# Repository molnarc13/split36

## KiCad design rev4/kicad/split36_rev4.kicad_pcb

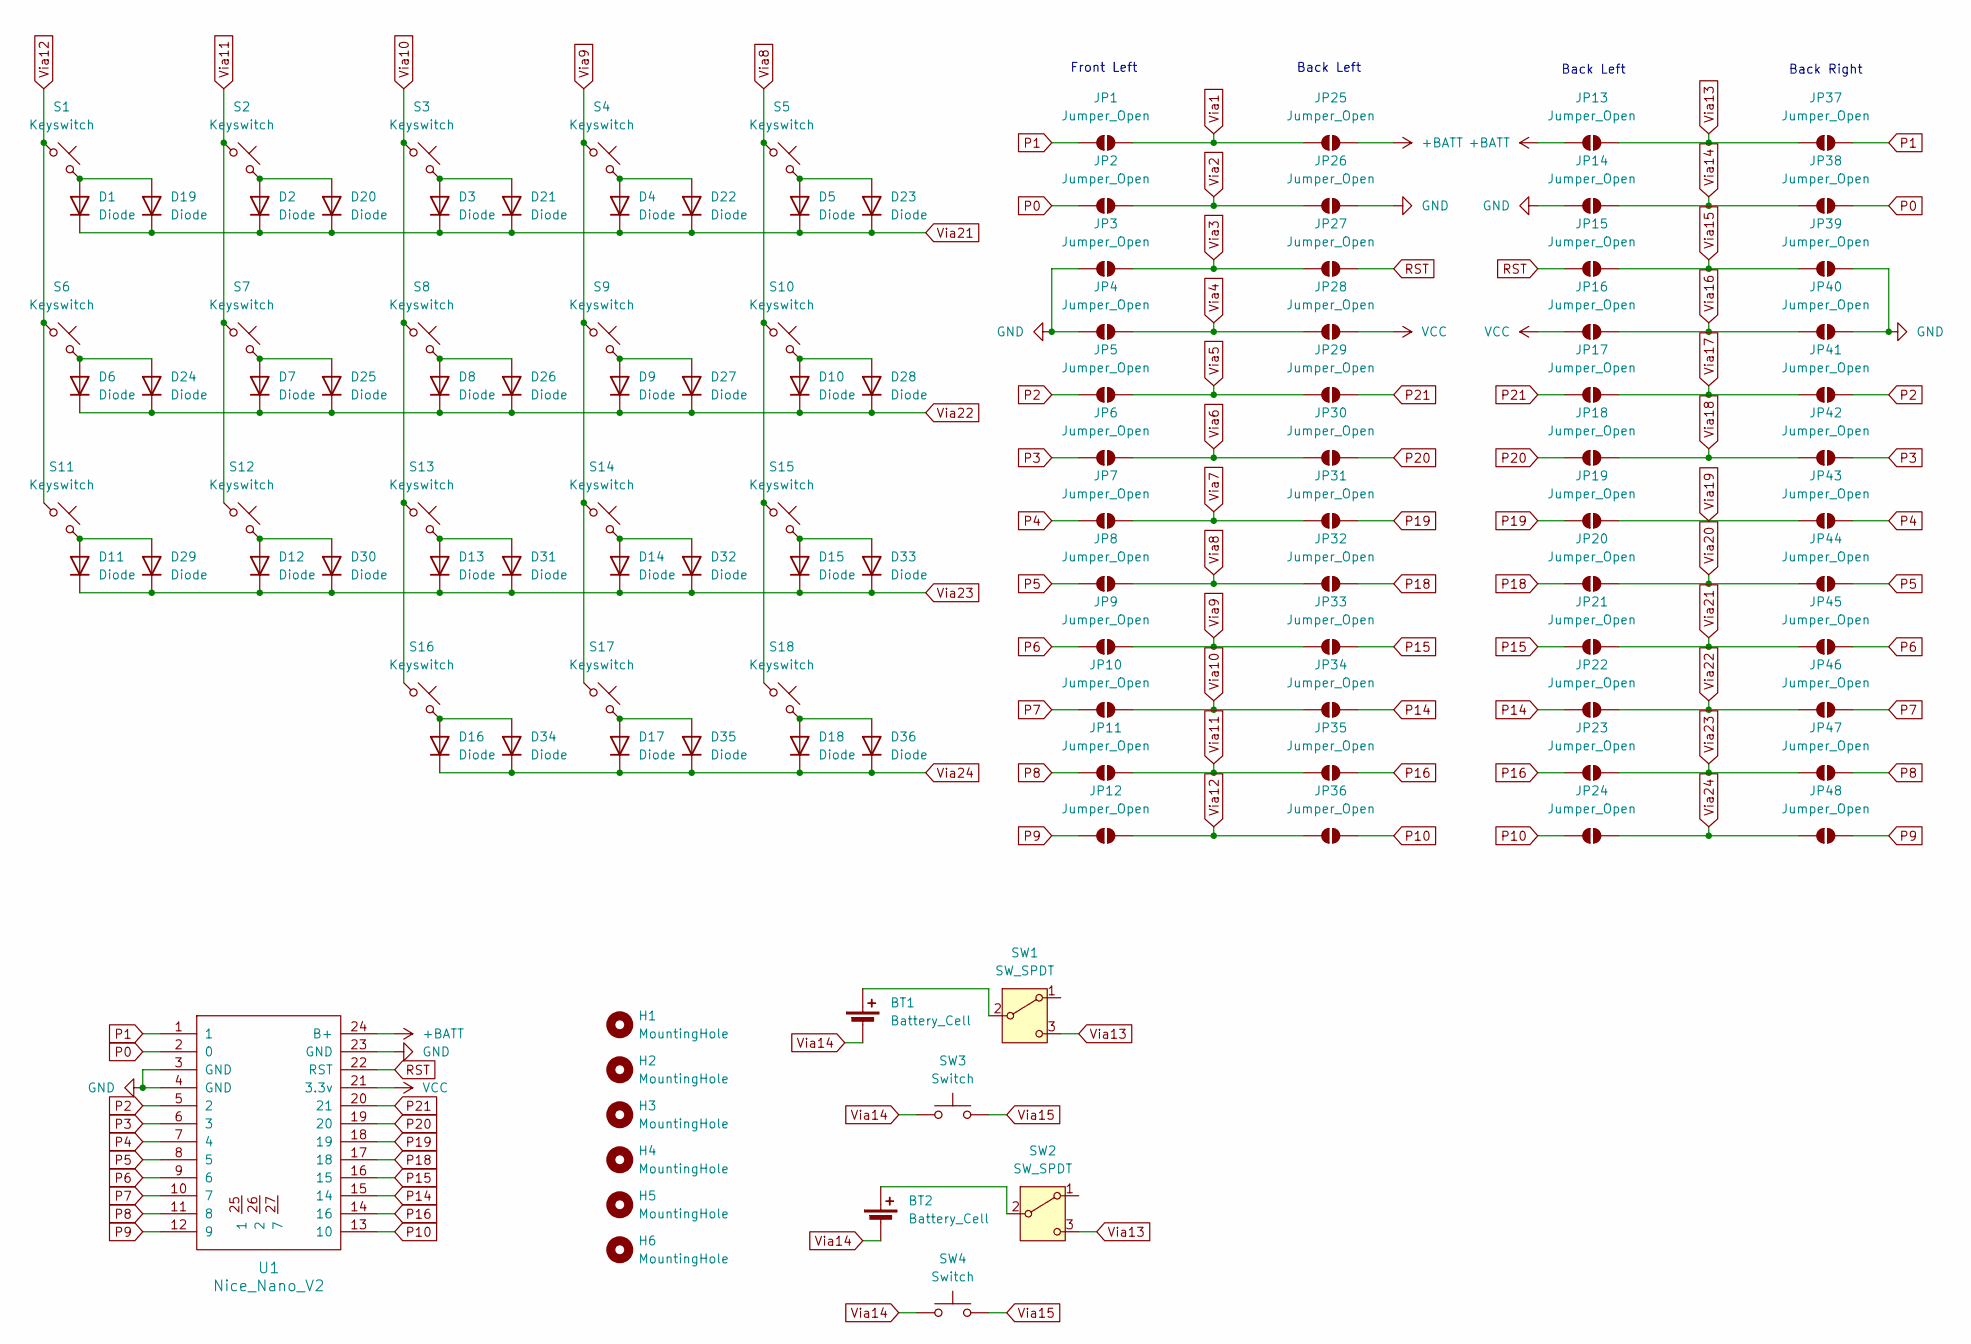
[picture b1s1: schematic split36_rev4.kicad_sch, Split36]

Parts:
BT1, BT2: Battery_Cell; JST_PH_S2B-PH-K_1x02_P2.00mm_Horizontal
D1, D2, D3, D4, D5, D6, D7, D8, D9, D10, D11, D12, D13, D14, D15, D16, D17, D18, D19, D20, D21, D22, D23, D24, D25, D26, D27, D28, D29, D30, D31, D32, D33, D34, D35, D36: Diode; Diode_SOD-123
H1, H2, H3, H4, H5, H6: MountingHole; Standoff_M2x6mm
JP1, JP2, JP3, JP4, JP5, JP6, JP7, JP8, JP9, JP10, JP11, JP12, JP13, JP14, JP15, JP16, JP17, JP18, JP19, JP20, JP21, JP22, JP23, JP24, JP25, JP26, JP27, JP28, JP29, JP30, JP31, JP32, JP33, JP34, JP35, JP36, JP37, JP38, JP39, JP40, JP41, JP42, JP43, JP44, JP45, JP46, JP47, JP48: Jumper_Open; SolderJumper-2_P1.3mm_Open_TrianglePad1.0x1.5mm
S1, S2, S3, S4, S5, S6, S7, S8, S9, S10, S11, S12, S13, S14, S15, S16, S17, S18: Keyswitch; Kailh_socket_PG1350_reversible
SW1, SW2: SW_SPDT; Switch_MSK12C02
SW3, SW4: Switch; SW_SPST_TL3342
U1: Nice_Nano_V2

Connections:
+BATT: JP13.1 (A), JP25.1 (A), U1.24 (B+)
GND: JP3.1 (A), JP4.1 (A), JP14.1 (A), JP26.1 (A), JP39.1 (A), JP40.1 (A), U1.3 (GND), U1.4 (GND), U1.23 (GND)
unnamed: BT1.1 (+), SW1.2 (B)
unnamed: BT2.1 (+), SW2.2 (B)
unnamed: D1.2 (A), D19.2 (A), S1.2
unnamed: D2.2 (A), D20.2 (A), S2.2
unnamed: D10.2 (A), D28.2 (A), S10.2
unnamed: D11.2 (A), D29.2 (A), S11.2
unnamed: D12.2 (A), D30.2 (A), S12.2
unnamed: D13.2 (A), D31.2 (A), S13.2
unnamed: D14.2 (A), D32.2 (A), S14.2
unnamed: D15.2 (A), D33.2 (A), S15.2
unnamed: D16.2 (A), D34.2 (A), S16.2
unnamed: D17.2 (A), D35.2 (A), S17.2
unnamed: D18.2 (A), D36.2 (A), S18.2
unnamed: D3.2 (A), D21.2 (A), S3.2
unnamed: D4.2 (A), D22.2 (A), S4.2
unnamed: D5.2 (A), D23.2 (A), S5.2
unnamed: D6.2 (A), D24.2 (A), S6.2
unnamed: D7.2 (A), D25.2 (A), S7.2
unnamed: D8.2 (A), D26.2 (A), S8.2
unnamed: D9.2 (A), D27.2 (A), S9.2
P0: JP2.1 (A), JP38.1 (A), U1.2 (0)
P1: JP1.1 (A), JP37.1 (A), U1.1
P2: JP5.1 (A), JP41.1 (A), U1.5 (2)
P3: JP6.1 (A), JP42.1 (A), U1.6 (3)
P4: JP7.1 (A), JP43.1 (A), U1.7 (4)
P5: JP8.1 (A), JP44.1 (A), U1.8 (5)
P6: JP9.1 (A), JP45.1 (A), U1.9 (6)
P7: JP10.1 (A), JP46.1 (A), U1.10 (7)
P8: JP11.1 (A), JP47.1 (A), U1.11 (8)
P9: JP12.1 (A), JP48.1 (A), U1.12 (9)
P10: JP24.1 (A), JP36.1 (A), U1.13 (10)
P14: JP22.1 (A), JP34.1 (A), U1.15 (14)
P15: JP21.1 (A), JP33.1 (A), U1.16 (15)
P16: JP23.1 (A), JP35.1 (A), U1.14 (16)
P18: JP20.1 (A), JP32.1 (A), U1.17 (18)
P19: JP19.1 (A), JP31.1 (A), U1.18 (19)
P20: JP18.1 (A), JP30.1 (A), U1.19 (20)
P21: JP17.1 (A), JP29.1 (A), U1.20 (21)
RST: JP15.1 (A), JP27.1 (A), U1.22 (RST)
VCC: JP16.1 (A), JP28.1 (A), U1.21 (3.3v)
Via1: JP1.2 (B), JP25.2 (B)
Via2: JP2.2 (B), JP26.2 (B)
Via3: JP3.2 (B), JP27.2 (B)
Via4: JP4.2 (B), JP28.2 (B)
Via5: JP5.2 (B), JP29.2 (B)
Via6: JP6.2 (B), JP30.2 (B)
Via7: JP7.2 (B), JP31.2 (B)
Via8: JP8.2 (B), JP32.2 (B), S5.1, S10.1, S15.1, S18.1
Via9: JP9.2 (B), JP33.2 (B), S4.1, S9.1, S14.1, S17.1
Via10: JP10.2 (B), JP34.2 (B), S3.1, S8.1, S13.1, S16.1
Via11: JP11.2 (B), JP35.2 (B), S2.1, S7.1, S12.1
Via12: JP12.2 (B), JP36.2 (B), S1.1, S6.1, S11.1
Via13: JP13.2 (B), JP37.2 (B), SW1.3 (C), SW2.3 (C)
Via14: BT1.2 (-), BT2.2 (-), JP14.2 (B), JP38.2 (B), SW3.1, SW4.1
Via15: JP15.2 (B), JP39.2 (B), SW3.2, SW4.2
Via16: JP16.2 (B), JP40.2 (B)
Via17: JP17.2 (B), JP41.2 (B)
Via18: JP18.2 (B), JP42.2 (B)
Via19: JP19.2 (B), JP43.2 (B)
Via20: JP20.2 (B), JP44.2 (B)
Via21: D1.1 (K), D2.1 (K), D3.1 (K), D4.1 (K), D5.1 (K), D19.1 (K), D20.1 (K), D21.1 (K), D22.1 (K), D23.1 (K), JP21.2 (B), JP45.2 (B)
Via22: D6.1 (K), D7.1 (K), D8.1 (K), D9.1 (K), D10.1 (K), D24.1 (K), D25.1 (K), D26.1 (K), D27.1 (K), D28.1 (K), JP22.2 (B), JP46.2 (B)
Via23: D11.1 (K), D12.1 (K), D13.1 (K), D14.1 (K), D15.1 (K), D29.1 (K), D30.1 (K), D31.1 (K), D32.1 (K), D33.1 (K), JP23.2 (B), JP47.2 (B)
Via24: D16.1 (K), D17.1 (K), D18.1 (K), D34.1 (K), D35.1 (K), D36.1 (K), JP24.2 (B), JP48.2 (B)

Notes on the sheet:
Back Left
Back Right
Front Left

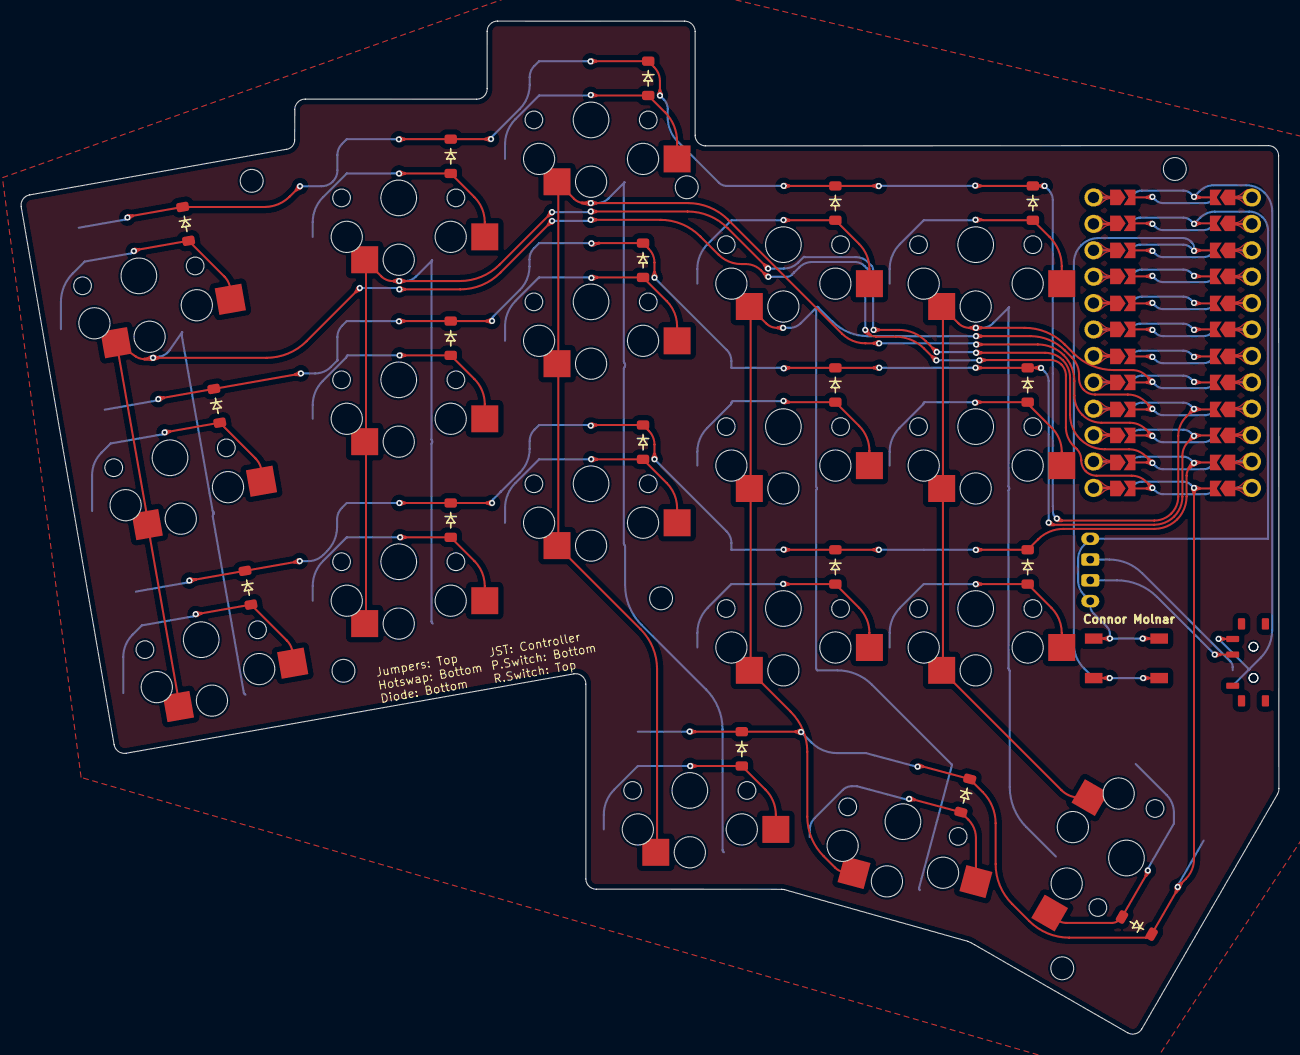
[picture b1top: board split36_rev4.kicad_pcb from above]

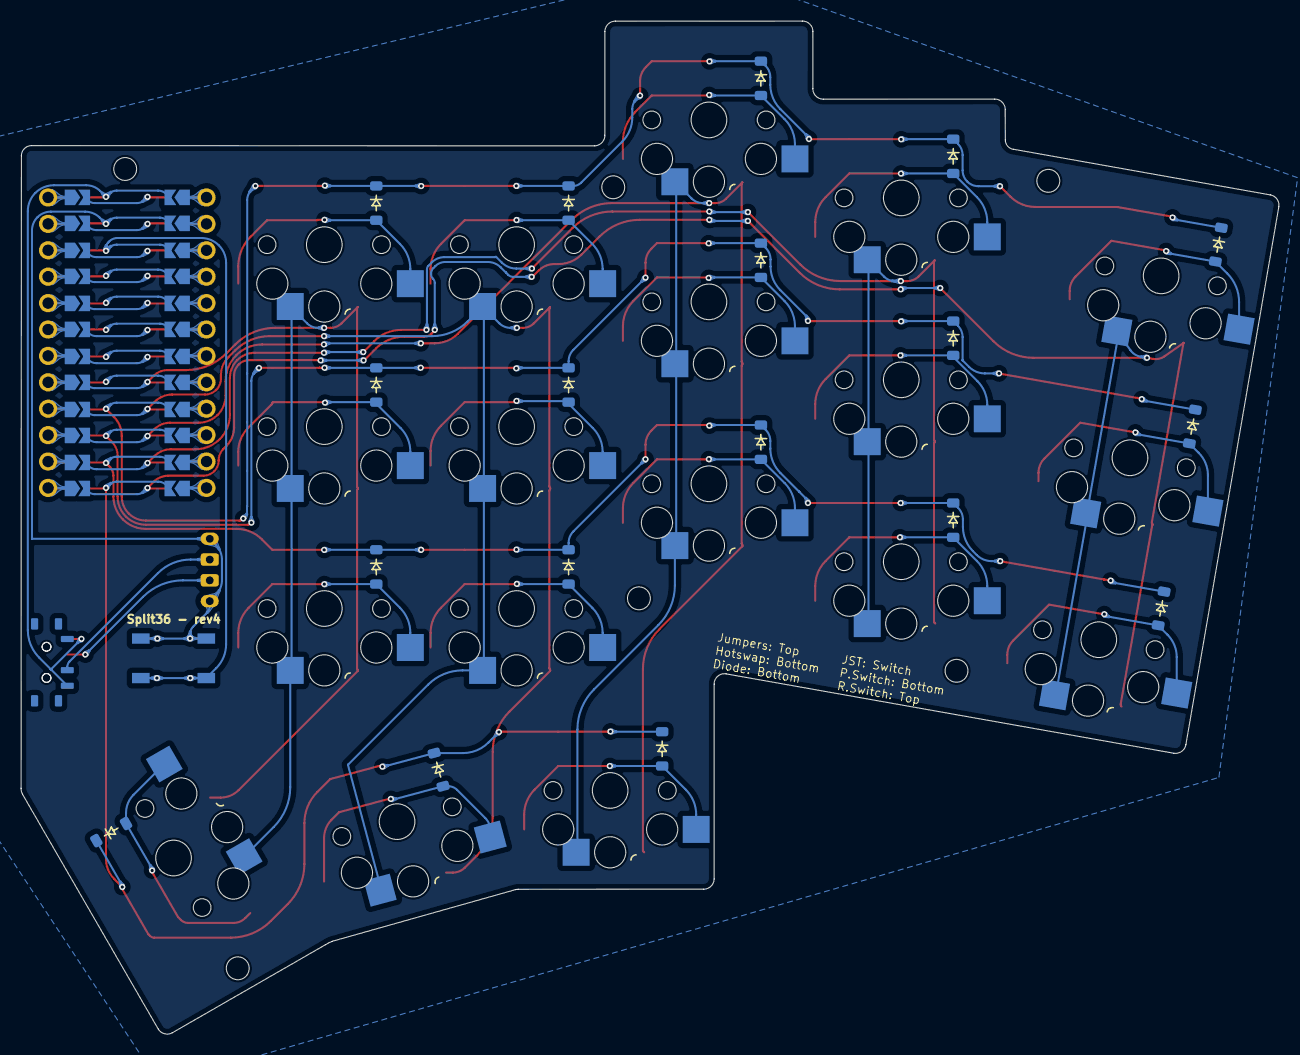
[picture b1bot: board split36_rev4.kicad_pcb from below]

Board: 2 copper layers, 121.0 x 97.4 mm, 115 parts (45 on the bottom side), 66 nets.

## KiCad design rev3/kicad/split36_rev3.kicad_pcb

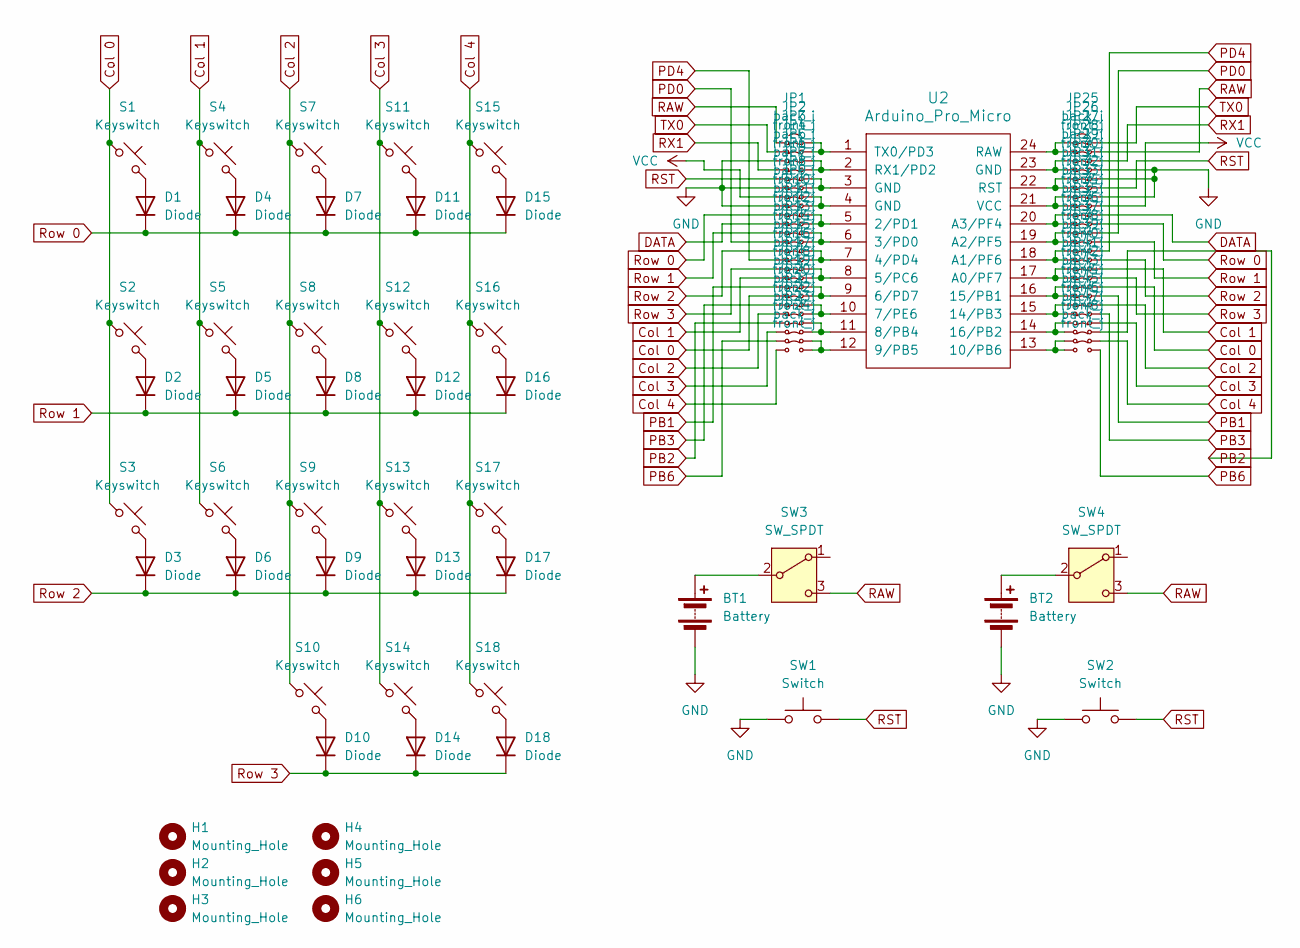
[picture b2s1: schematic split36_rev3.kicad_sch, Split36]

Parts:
BT1, BT2: Battery; JST_PH_S2B-PH-K_1x02_P2.00mm_Horizontal
D1, D2, D3, D4, D5, D6, D7, D8, D9, D10, D11, D12, D13, D14, D15, D16, D17, D18: Diode; Diode_DO-35
H1, H2, H3, H4, H5, H6: Mounting_Hole; Standoff_M2x6mm
JP1, JP3, JP5, JP7, JP9, JP11, JP13, JP15, JP17, JP19, JP21, JP23, JP25, JP27, JP29, JP31, JP33, JP35, JP37, JP39, JP41, JP43, JP45, JP47: back_j; SolderJumper-2_P1.3mm_Open_TrianglePad1.0x1.5mm
JP2, JP4, JP6, JP8, JP10, JP12, JP14, JP16, JP18, JP20, JP22, JP24, JP26, JP28, JP30, JP32, JP34, JP36, JP38, JP40, JP42, JP44, JP46, JP48: front_j; SolderJumper-2_P1.3mm_Open_TrianglePad1.0x1.5mm
S1, S2, S3, S4, S5, S6, S7, S8, S9, S10, S11, S12, S13, S14, S15, S16, S17, S18: Keyswitch; Kailh_socket_PG1350_reversible
SW1, SW2: Switch; Button_TL3342
SW3, SW4: SW_SPDT; Switch_MSK12C02
U2: Arduino_Pro_Micro

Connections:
Col 0: JP18.2 (B), JP41.2 (B), S1.1, S2.1, S3.1
Col 1: JP16.2 (B), JP39.2 (B), S4.1, S5.1, S6.1
Col 2: JP20.2 (B), JP43.2 (B), S7.1, S8.1, S9.1, S10.1
Col 3: JP22.2 (B), JP45.2 (B), S11.1, S12.1, S13.1, S14.1
Col 4: JP24.2 (B), JP47.2 (B), S15.1, S16.1, S17.1, S18.1
DATA: JP10.2 (B), JP33.2 (B)
GND: BT1.2 (-), BT2.2 (-), JP3.2 (B), JP6.2 (B), JP8.2 (B), JP28.2 (B), JP29.2 (B), JP31.2 (B), SW1.1, SW2.1
unnamed: BT1.1 (+), SW3.2 (B)
unnamed: BT2.1 (+), SW4.2 (B)
unnamed: D1.2 (A), S1.2
unnamed: D2.2 (A), S2.2
unnamed: D3.2 (A), S3.2
unnamed: D4.2 (A), S4.2
unnamed: D5.2 (A), S5.2
unnamed: D6.2 (A), S6.2
unnamed: D7.2 (A), S7.2
unnamed: D8.2 (A), S8.2
unnamed: D9.2 (A), S9.2
unnamed: D10.2 (A), S10.2
unnamed: D11.2 (A), S11.2
unnamed: D12.2 (A), S12.2
unnamed: D13.2 (A), S13.2
unnamed: D14.2 (A), S14.2
unnamed: D15.2 (A), S15.2
unnamed: D16.2 (A), S16.2
unnamed: D17.2 (A), S17.2
unnamed: D18.2 (A), S18.2
unnamed: JP1.1 (A), JP2.1 (A), U2.1 (TX0/PD3)
unnamed: JP3.1 (A), JP4.1 (A), U2.2 (RX1/PD2)
unnamed: JP5.1 (A), JP6.1 (A), U2.3 (GND)
unnamed: JP7.1 (A), JP8.1 (A), U2.4 (GND)
unnamed: JP9.1 (A), JP10.1 (A), U2.5 (2/PD1)
unnamed: JP11.1 (A), JP12.1 (A), U2.6 (3/PD0)
unnamed: JP13.1 (A), JP14.1 (A), U2.7 (4/PD4)
unnamed: JP15.1 (A), JP16.1 (A), U2.8 (5/PC6)
unnamed: JP17.1 (A), JP18.1 (A), U2.9 (6/PD7)
unnamed: JP19.1 (A), JP20.1 (A), U2.10 (7/PE6)
unnamed: JP21.1 (A), JP22.1 (A), U2.11 (8/PB4)
unnamed: JP23.1 (A), JP24.1 (A), U2.12 (9/PB5)
unnamed: JP25.1 (A), JP26.1 (A), U2.24 (RAW)
unnamed: JP27.1 (A), JP28.1 (A), U2.23 (GND)
unnamed: JP29.1 (A), JP30.1 (A), U2.22 (RST)
unnamed: JP31.1 (A), JP32.1 (A), U2.21 (VCC)
unnamed: JP33.1 (A), JP34.1 (A), U2.20 (A3/PF4)
unnamed: JP35.1 (A), JP36.1 (A), U2.19 (A2/PF5)
unnamed: JP37.1 (A), JP38.1 (A), U2.18 (A1/PF6)
unnamed: JP39.1 (A), JP40.1 (A), U2.17 (A0/PF7)
unnamed: JP41.1 (A), JP42.1 (A), U2.16 (15/PB1)
unnamed: JP43.1 (A), JP44.1 (A), U2.15 (14/PB3)
unnamed: JP45.1 (A), JP46.1 (A), U2.14 (16/PB2)
unnamed: JP47.1 (A), JP48.1 (A), U2.13 (10/PB6)
PB1: JP17.2 (B), JP42.2 (B)
PB2: JP21.2 (B), JP46.2 (B)
PB3: JP19.2 (B), JP44.2 (B)
PB6: JP23.2 (B), JP48.2 (B)
PD0: JP12.2 (B), JP35.2 (B)
PD4: JP14.2 (B), JP37.2 (B)
RAW: JP1.2 (B), JP26.2 (B), SW3.3 (C), SW4.3 (C)
RST: JP5.2 (B), JP30.2 (B), SW1.2, SW2.2
RX1: JP4.2 (B), JP27.2 (B)
Row 0: D1.1 (K), D4.1 (K), D7.1 (K), D11.1 (K), D15.1 (K), JP9.2 (B), JP34.2 (B)
Row 1: D2.1 (K), D5.1 (K), D8.1 (K), D12.1 (K), D16.1 (K), JP11.2 (B), JP36.2 (B)
Row 2: D3.1 (K), D6.1 (K), D9.1 (K), D13.1 (K), D17.1 (K), JP13.2 (B), JP38.2 (B)
Row 3: D10.1 (K), D14.1 (K), D18.1 (K), JP15.2 (B), JP40.2 (B)
TX0: JP2.2 (B), JP25.2 (B)
VCC: JP7.2 (B), JP32.2 (B)

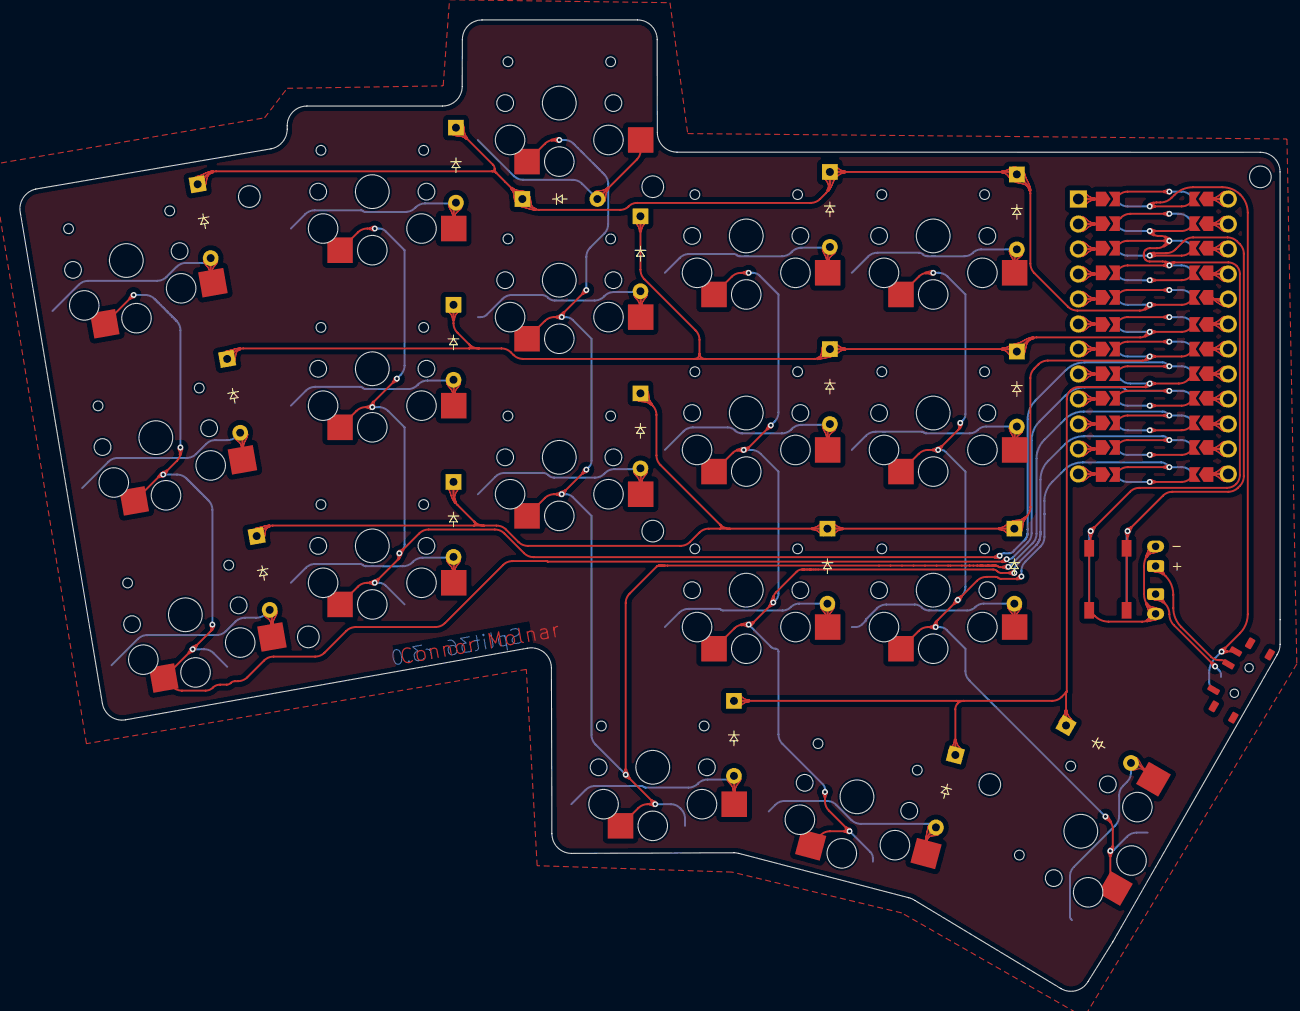
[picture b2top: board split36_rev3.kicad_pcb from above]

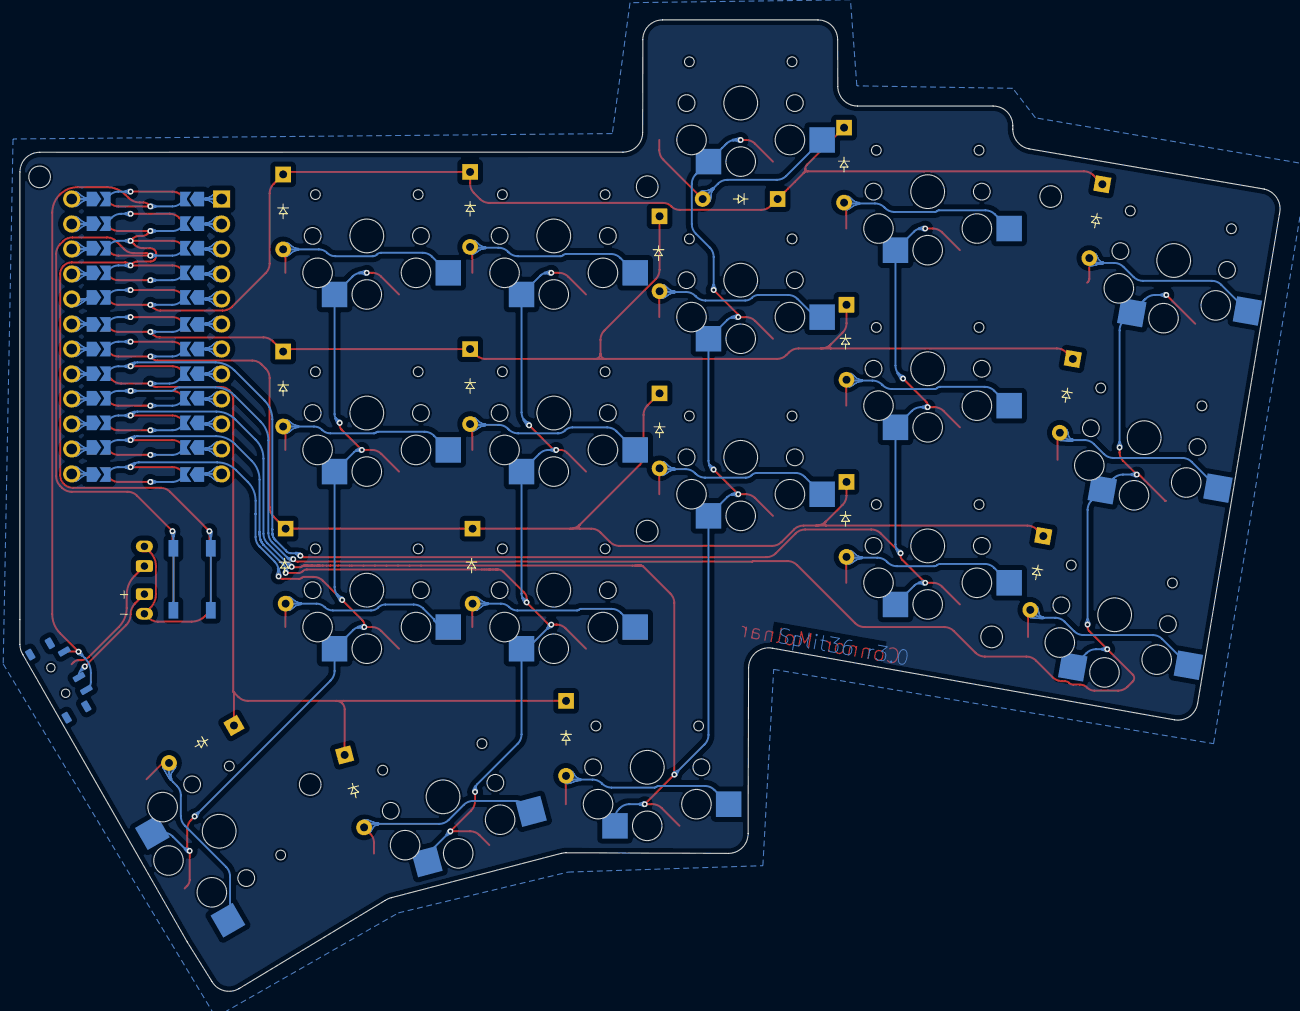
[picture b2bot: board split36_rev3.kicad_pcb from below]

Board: 2 copper layers, 128.1 x 98.7 mm, 97 parts (27 on the bottom side), 66 nets.

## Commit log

2024-07-29 adding rev3 kicad and 3dprint files
2024-07-30 adding gitignore and starting rev4
2024-07-30 rev4 kicad complete
2024-07-31 wrapping up 3d prints for rev4
2024-07-31 modifying case print for power switch
